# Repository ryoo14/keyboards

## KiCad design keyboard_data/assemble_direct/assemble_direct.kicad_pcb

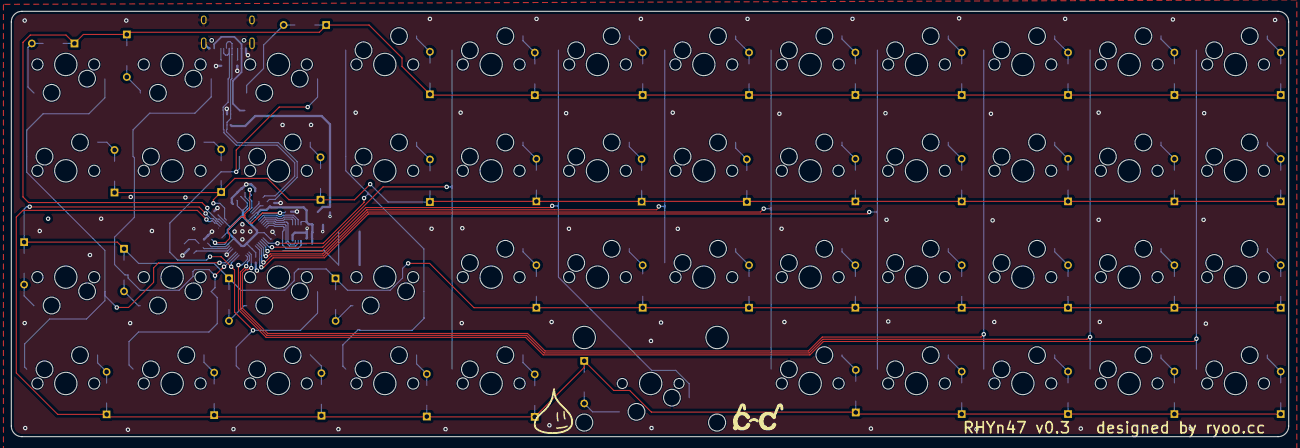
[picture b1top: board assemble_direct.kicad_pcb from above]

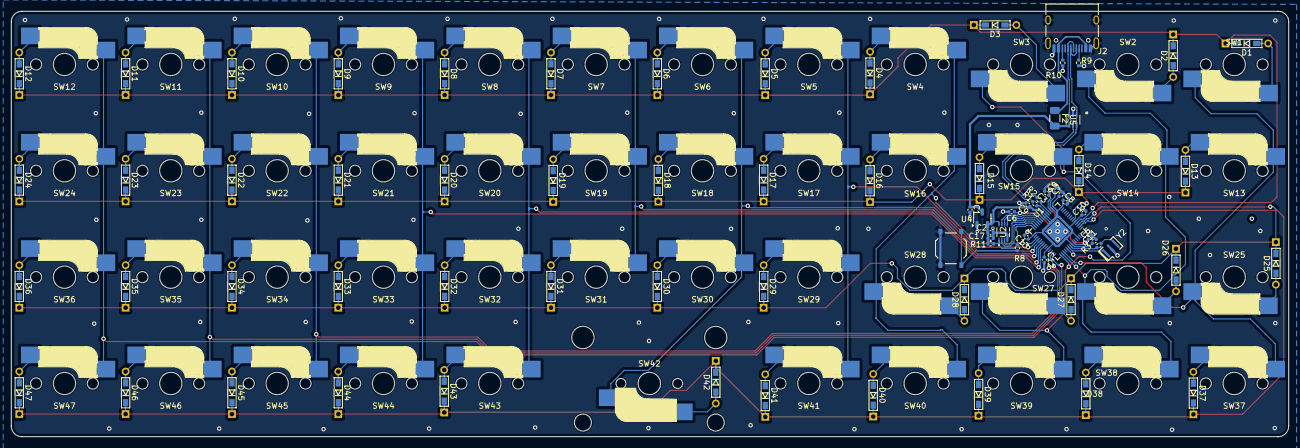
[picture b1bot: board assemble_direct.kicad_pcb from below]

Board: 2 copper layers, 228.8 x 76.2 mm, 123 parts (29 on the bottom side), 84 nets.

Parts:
C1, C2: 10uF; C_0402_1005Metric
C3, C4: 2.2uF; C_0402_1005Metric
C5, C6, C7, C8, C9, C10, C11, C12, C13: 100n; C_0402_1005Metric
C17: 100nF; C_0402_1005Metric
D1, D2, D3, D4, D5, D6, D7, D8, D9, D10, D11, D12, D13, D14, D15, D16, D17, D18, D19, D20, D21, D22, D23, D24, D25, D26, D27, D28, D29, D30, D31, D32, D33, D34, D35, D36, D37, D38, D39, D40, D41, D42, D43, D44, D45, D46, D47: D; Diode_TH_SMD
F2: fuse; Fuse_1206_3216Metric
J2: USB_C_Receptacle_USB2.0_16P; USB_C_Receptacle_HRO_TYPE-C-31-M-12
R1, R2: 27; R_0402_1005Metric
R3: 1k; R_0402_1005Metric
R8: 1KΩ; R_0402_1005Metric
R9, R10: 5.1k; R_0402_1005Metric
R11: 10kΩ; R_0402_1005Metric
SW1, SW2, SW3, SW4, SW5, SW6, SW7, SW8, SW9, SW10, SW11, SW12, SW13, SW14, SW15, SW16, SW17, SW18, SW19, SW20, SW21, SW22, SW23, SW24, SW25, SW26, SW27, SW28, SW29, SW30, SW31, SW32, SW33, SW34, SW35, SW36, SW37, SW38, SW39, SW40, SW41, SW43, SW44, SW45, SW46, SW47: SW_PUSH; CherryMX_Hotswap_1u
SW42: SW_PUSH; CherryMX_Hotswap_2u
SW48: boot; SW_Push_1P1T_XKB_TS-1187A
U1: RP2040; QFN-56-1EP_7x7mm_P0.4mm_EP3.2x3.2mm
U2: W25Q16JVUXIQ; W25Q16JVUXIQ_WIN
U4: XC6206P332MR; SOT-23-3
U5: SMF05CT1G; SOT-363-6_2P2X1P35_ONS
Y2: 12MHz; Resonator_SMD_Murata_CSTxExxV-3Pin_3.0x1.1mm

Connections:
+1V1: C3.1, C5.1, C6.1, U1.23 (DVDD), U1.45 (VREG_VOUT), U1.50 (DVDD)
+3V3: C2.1, C4.1, C7.1, C8.1, C9.1, C10.1, C11.1, C12.1, C13.1, C17.1, R11.2, U1.1 (IOVDD), U1.10 (IOVDD), U1.22 (IOVDD), U1.26 (RUN), U1.33 (IOVDD), U1.42 (IOVDD), U1.43 (ADC_AVDD), U1.44 (VREG_IN), U1.48 (USB_VDD), U1.49 (IOVDD), U2.8 (VCC), U4.2 (VO)
+5V: C1.1, F2.2, U4.3 (VI), U5.4 (CATHODE)
Col0: SW1.1, SW13.1, SW25.1, SW37.1, U1.17 (GPIO14)
Col1: SW2.1, SW14.1, SW26.1, SW38.1, U1.16 (GPIO13)
Col2: SW3.1, SW15.1, SW27.1, SW39.1, U1.15 (GPIO12)
Col3: SW4.1, SW16.1, SW28.1, SW40.1, U1.3 (GPIO1)
Col4: SW5.1, SW17.1, SW29.1, SW41.1, U1.4 (GPIO2)
Col5: SW6.1, SW18.1, SW30.1, SW42.1, U1.5 (GPIO3)
Col6: SW7.1, SW19.1, SW31.1, U1.6 (GPIO4)
Col7: SW8.1, SW20.1, SW32.1, SW43.1, U1.7 (GPIO5)
Col8: SW9.1, SW21.1, SW33.1, SW44.1, U1.8 (GPIO6)
Col9: SW10.1, SW22.1, SW34.1, SW45.1, U1.12 (GPIO9)
Col10: SW11.1, SW23.1, SW35.1, SW46.1, U1.13 (GPIO10)
Col11: SW12.1, SW24.1, SW36.1, SW47.1, U1.14 (GPIO11)
D+: J2.A6 (D+), J2.B6 (D+), R1.1, U5.3 (CATHODE), U5.5 (CATHODE)
D-: J2.A7 (D-), J2.B7 (D-), R2.1, U5.1 (CATHODE), U5.6 (CATHODE)
GND: C1.2, C2.2, C3.2, C4.2, C5.2, C6.2, C7.2, C8.2, C9.2, C10.2, C11.2, C12.2, C13.2, C17.2, J2.A1 (GND), J2.A12 (GND), J2.B1 (GND), J2.B12 (GND), J2.S1 (SHIELD), R9.1, R10.1, SW48.2, U1.19 (TESTEN), U1.57 (GND), U2.4 (GND), U2.9 (EPAD), U4.1 (GND), U5.2 (ANODE), Y2.2
unnamed: D1.2 (A), SW1.2
unnamed: D2.2 (A), SW2.2
unnamed: D3.2 (A), SW3.2
unnamed: D4.2 (A), SW4.2
unnamed: D5.2 (A), SW5.2
unnamed: D6.2 (A), SW6.2
unnamed: D7.2 (A), SW7.2
unnamed: D8.2 (A), SW8.2
unnamed: D9.2 (A), SW9.2
unnamed: D10.2 (A), SW10.2
unnamed: D11.2 (A), SW11.2
unnamed: D12.2 (A), SW12.2
unnamed: D13.2 (A), SW13.2
unnamed: D14.2 (A), SW14.2
unnamed: D15.2 (A), SW15.2
unnamed: D16.2 (A), SW16.2
unnamed: D17.2 (A), SW17.2
unnamed: D18.2 (A), SW18.2
unnamed: D19.2 (A), SW19.2
unnamed: D20.2 (A), SW20.2
unnamed: D21.2 (A), SW21.2
unnamed: D22.2 (A), SW22.2
unnamed: D23.2 (A), SW23.2
unnamed: D24.2 (A), SW24.2
unnamed: D25.2 (A), SW25.2
unnamed: D26.2 (A), SW26.2
unnamed: D27.2 (A), SW27.2
unnamed: D28.2 (A), SW28.2
unnamed: D29.2 (A), SW29.2
unnamed: D30.2 (A), SW30.2
unnamed: D31.2 (A), SW31.2
unnamed: D32.2 (A), SW32.2
unnamed: D33.2 (A), SW33.2
unnamed: D34.2 (A), SW34.2
unnamed: D35.2 (A), SW35.2
unnamed: D36.2 (A), SW36.2
unnamed: D37.2 (A), SW37.2
unnamed: D38.2 (A), SW38.2
unnamed: D39.2 (A), SW39.2
unnamed: D40.2 (A), SW40.2
unnamed: D41.2 (A), SW41.2
unnamed: D42.2 (A), SW42.2
unnamed: D43.2 (A), SW43.2
unnamed: D44.2 (A), SW44.2
unnamed: D45.2 (A), SW45.2
unnamed: D46.2 (A), SW46.2
unnamed: D47.2 (A), SW47.2
unnamed: J2.A5 (CC1), R9.2
unnamed: J2.B5 (CC2), R10.2
unnamed: R3.1, Y2.3
unnamed: R2.2, U1.46 (USB_DM)
unnamed: R1.2, U1.47 (USB_DP)
unnamed: U1.20 (XIN), Y2.1
unnamed: R3.2, U1.21 (XOUT)
QSPI_SCLK: U1.52 (QSPI_SCLK), U2.6 (CLK)
QSPI_SD0: U1.53 (QSPI_SD0), U2.5 (DI(IO0))
QSPI_SD1: U1.55 (QSPI_SD1), U2.2 (DO(IO1))
QSPI_SD2: U1.54 (QSPI_SD2), U2.3 (/WP(IO2))
QSPI_SD3: U1.51 (QSPI_SD3), U2.7 (/HOLD_or_/RESET(IO3))
QSPI_SS: R8.1, R11.1, U1.56 (QSPI_SS), U2.1 (/CS)
Row0: D1.1 (K), D2.1 (K), D3.1 (K), D4.1 (K), D5.1 (K), D6.1 (K), D7.1 (K), D8.1 (K), D9.1 (K), D10.1 (K), D11.1 (K), D12.1 (K), U1.32 (GPIO21)
Row1: D13.1 (K), D14.1 (K), D15.1 (K), D16.1 (K), D17.1 (K), D18.1 (K), D19.1 (K), D20.1 (K), D21.1 (K), D22.1 (K), D23.1 (K), D24.1 (K), U1.34 (GPIO22)
Row2: D25.1 (K), D26.1 (K), D27.1 (K), D28.1 (K), D29.1 (K), D30.1 (K), D31.1 (K), D32.1 (K), D33.1 (K), D34.1 (K), D35.1 (K), D36.1 (K), U1.31 (GPIO20)
Row3: D37.1 (K), D38.1 (K), D39.1 (K), D40.1 (K), D41.1 (K), D42.1 (K), D43.1 (K), D44.1 (K), D45.1 (K), D46.1 (K), D47.1 (K), U1.30 (GPIO19)
USB_BOOT: R8.2, SW48.1
VBUS: F2.1, J2.A4 (VBUS), J2.A9 (VBUS), J2.B4 (VBUS), J2.B9 (VBUS)

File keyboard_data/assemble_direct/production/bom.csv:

Designator,Footprint,Quantity,Value,LCSC Part #
"C1, C2",0402,2,10uF,C15525
"C10, C11, C12, C13, C7, C8, C9",0402,7,100n,C1525
C17,0402,1,100nF,C1525
C3,0402,1,2.2uF,C307418
C4,0402,1,2.2uF,C307418
"C5, C6",0402,2,100n,C1525
"D1, D10, D11, D12, D13, D14, D15, D16, D17, D18, D19, D2, D20, D21, D22, D23, D24, D25, D26, D27, D28, D29, D3, D30, D31, D32, D33, D34, D35, D36, D37, D38, D39, D4, D40, D41, D42, D43, D44, D45, D46, D47, D5, D6, D7, D8, D9",Diode_TH_SMD,47,D,C81598
F2,1206,1,fuse,C70076
J2,USB_C_Receptacle_HRO_TYPE-C-31-M-12,1,USB_C_Receptacle_USB2.0_16P,C165948
"R1, R2",0402,2,27,C25190
"R10, R9",0402,2,5.1k,C25905
R11,0402,1,10kΩ,C25744
R3,0402,1,1k,C11702
R8,0402,1,1KΩ,C11702
SW48,SW_Push_1P1T_XKB_TS-1187A,1,boot,C318884
U1,QFN-56-1EP_7x7mm_P0.4mm_EP3.2x3.2mm,1,RP2040,C2040
U2,W25Q16JVUXIQ_WIN,1,W25Q16JVUXIQ,C2843335
U4,SOT-23-3,1,XC6206P332MR,C5446
U5,SOT-363-6_2P2X1P35_ONS,1,SMF05CT1G,C15879
Y2,Resonator_SMD_Murata_CSTxExxV-3Pin_3.0x1.1mm,1,12MHz,C341520
